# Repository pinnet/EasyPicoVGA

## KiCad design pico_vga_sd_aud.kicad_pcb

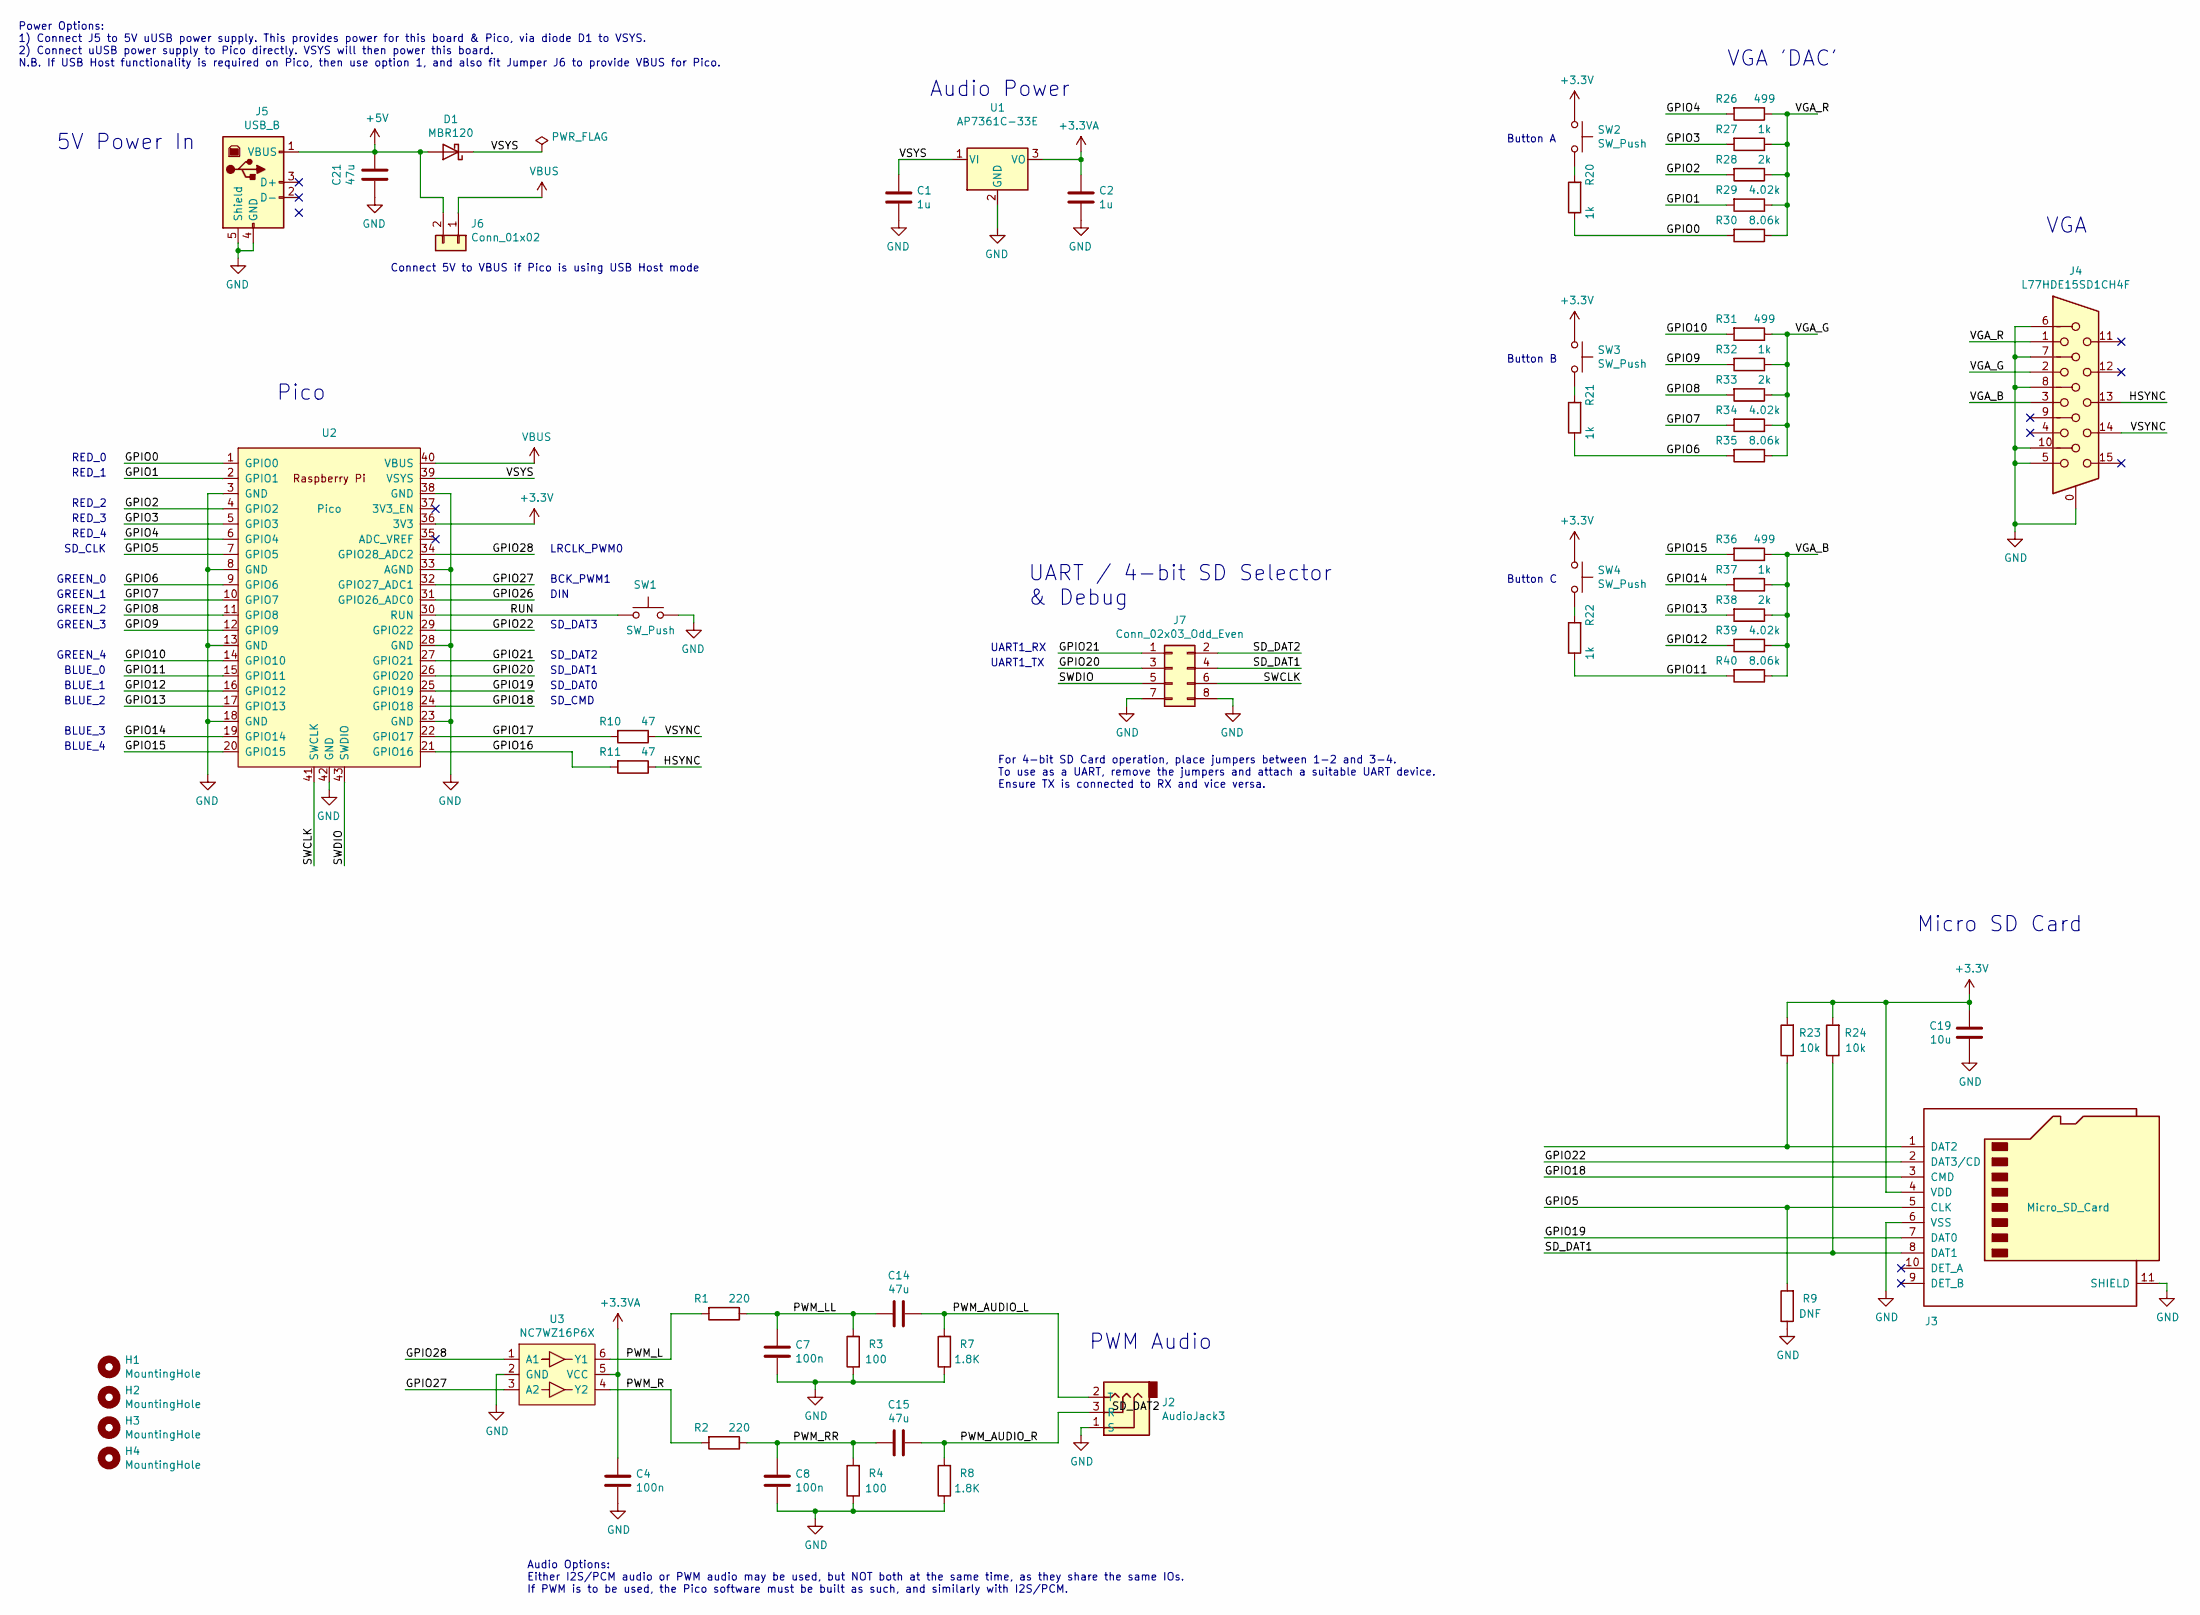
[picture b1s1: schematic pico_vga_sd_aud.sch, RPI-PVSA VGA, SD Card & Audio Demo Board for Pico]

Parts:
C1, C2: 1u; C_Disc_D4.7mm_W2.5mm_P5.00mm
C4, C7, C8: 100n; C_Disc_D4.7mm_W2.5mm_P5.00mm
C14, C15, C21: 47u; CP_Radial_D5.0mm_P2.50mm
C19: 10u; CP_Radial_D6.3mm_P2.50mm
D1: MBR120; D_A-405_P12.70mm_Horizontal
H1, H2, H3, H4: MountingHole; MountingHole_2.7mm_M2.5
J2: AudioJack3; CUI_SJ-3523-audio-jack
J3: Micro_SD_Card; microSD_HC_Molex_104031-0811
J4: L77HDE15SD1CH4F; DSUB-15-L77HDE15SD1CH4F
J5: USB_B; USB_B_Lumberg_2411_02_Horizontal
J6: Conn_01x02; PinHeader_1x02_P2.54mm_Vertical
J7: Conn_02x03_Odd_Even; PinHeader_2x04_P2.54mm_Vertical
R1, R2: 220; R_Axial_DIN0207_L6.3mm_D2.5mm_P15.24mm_Horizontal
R3, R4: 100; R_Axial_DIN0207_L6.3mm_D2.5mm_P15.24mm_Horizontal
R7, R8: 1.8K; R_Axial_DIN0207_L6.3mm_D2.5mm_P15.24mm_Horizontal
R9: DNF; R_Axial_DIN0207_L6.3mm_D2.5mm_P15.24mm_Horizontal
R10, R11: 47; R_Axial_DIN0207_L6.3mm_D2.5mm_P15.24mm_Horizontal
R20, R21, R22, R27, R32, R37: 1k; R_Axial_DIN0207_L6.3mm_D2.5mm_P15.24mm_Horizontal
R23, R24: 10k; R_Axial_DIN0207_L6.3mm_D2.5mm_P15.24mm_Horizontal
R26, R31, R36: 499; R_Axial_DIN0207_L6.3mm_D2.5mm_P15.24mm_Horizontal
R28, R33, R38: 2k; R_Axial_DIN0207_L6.3mm_D2.5mm_P15.24mm_Horizontal
R29, R34, R39: 4.02k; R_Axial_DIN0207_L6.3mm_D2.5mm_P15.24mm_Horizontal
R30, R35, R40: 8.06k; R_Axial_DIN0207_L6.3mm_D2.5mm_P15.24mm_Horizontal
SW1, SW2, SW3, SW4: SW_Push; SW_Tactile_SPST_Angled_PTS645Vx83-2LFS
U1: AP7361C-33E; TO-92_Inline
U2: Pico; RPi_Pico_SMD_TH
U3: NC7WZ16P6X; SOT-363_SC-70-6

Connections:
+3.3VA: C2.1, C4.1, U1.3 (VO), U3.5 (VCC)
+3V3: C19.1, J3.4 (VDD), R23.2, R24.2, SW2.1, SW3.1, SW4.1, U2.36 (3V3)
+5V: C21.1, D1.2 (A), J5.1 (VBUS), J6.2
/GPIO0: R20.1, R30.2, U2.1 (GPIO0)
/GPIO1: R29.2, U2.2 (GPIO1)
/GPIO2: R28.2, U2.4 (GPIO2)
/GPIO3: R27.2, U2.5 (GPIO3)
/GPIO4: R26.2, U2.6 (GPIO4)
/GPIO5: J3.5 (CLK), R9.2, U2.7 (GPIO5)
/GPIO6: R21.1, R35.2, U2.9 (GPIO6)
/GPIO7: R34.2, U2.10 (GPIO7)
/GPIO8: R33.2, U2.11 (GPIO8)
/GPIO9: R32.2, U2.12 (GPIO9)
/GPIO10: R31.2, U2.14 (GPIO10)
/GPIO11: R22.1, R40.2, U2.15 (GPIO11)
/GPIO12: R39.2, U2.16 (GPIO12)
/GPIO13: R38.2, U2.17 (GPIO13)
/GPIO14: R37.2, U2.19 (GPIO14)
/GPIO15: R36.2, U2.20 (GPIO15)
/GPIO16: R11.2, U2.21 (GPIO16)
/GPIO17: R10.2, U2.22 (GPIO17)
/GPIO18: J3.3 (CMD), U2.24 (GPIO18)
/GPIO19: J3.7 (DAT0), U2.25 (GPIO19)
/GPIO20: J7.3, U2.26 (GPIO20)
/GPIO21: J7.1, U2.27 (GPIO21)
/GPIO22: J3.2 (DAT3/CD), U2.29 (GPIO22)
/GPIO26: U2.31 (GPIO26_ADC0)
/GPIO27: U2.32 (GPIO27_ADC1), U3.3 (A2)
/GPIO28: U2.34 (GPIO28_ADC2), U3.1 (A1)
/HSYNC: J4.13, R11.1
/PWM_AUDIO_L: C14.1, J2.2 (T), R7.2
/PWM_AUDIO_R: C15.1, J2.3 (R), R8.2
/PWM_L: R1.2, U3.6 (Y1)
/PWM_LL: C7.1, C14.2, R1.1, R3.2
/PWM_R: R2.2, U3.4 (Y2)
/PWM_RR: C8.1, C15.2, R2.1, R4.2
/RUN: SW1.1, U2.30 (RUN)
/SD_DAT1: J3.8 (DAT1), J7.4, R24.1
/SD_DAT2: J7.2
/SWCLK: J7.6, U2.41 (SWCLK)
/SWDIO: J7.5, U2.43 (SWDIO)
/VGA_B: J4.3, R36.1, R37.1, R38.1, R39.1, R40.1
/VGA_G: J4.2, R31.1, R32.1, R33.1, R34.1, R35.1
/VGA_R: J4.1, R26.1, R27.1, R28.1, R29.1, R30.1
/VSYNC: J4.14, R10.1
/VSYS: C1.1, D1.1 (K), U1.1 (VI), U2.39 (VSYS)
GND: C1.2, C2.2, C4.2, C7.2, C8.2, C19.2, C21.2, J2.1 (S), J3.6 (VSS), J3.11 (SHIELD), J4.0, J4.5, J4.6, J4.7, J4.8, J4.10, J5.4 (GND), J5.5 (Shield), J7.7, J7.8, R3.1, R4.1, R7.1, R8.1, R9.1, SW1.2, U1.2 (GND), U2.3 (GND), U2.8 (GND), U2.13 (GND), U2.18 (GND), U2.23 (GND), U2.28 (GND), U2.33 (AGND), U2.38 (GND), U2.42 (GND), U3.2 (GND)
unnamed: J3.1 (DAT2), R23.1
unnamed: R20.2, SW2.2
unnamed: R21.2, SW3.2
unnamed: R22.2, SW4.2
VBUS: J6.1, U2.40 (VBUS)

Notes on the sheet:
Pico
Audio Power
PWM Audio
Micro SD Card
VGA
Connect 5V to VBUS if Pico is using USB Host mode
5V Power In
Power Options: 1) Connect J5 to 5V uUSB power supply. This provides power for this board & Pico, via diode D1 to VSYS. 2) Connect uUSB power supply to Pico directly. VSYS will then power this board. N.B. If USB Host functionality is required on Pico, then use option 1, and also fit Jumper J6 to pro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
VGA 'DAC'
Button A
Button B
Button C
SD_CLK
SD_CMD
SD_DAT0
SD_DAT1
SD_DAT2
SD_DAT3
DIN
BCK_PWM1
LRCLK_PWM0
RED_0
RED_1
RED_2
RED_3
RED_4
GREEN_0
GREEN_1
GREEN_2
GREEN_3
GREEN_4
BLUE_0
BLUE_1
BLUE_2
BLUE_3
BLUE_4
UART1_TX
UART1_RX
UART / 4-bit SD Selector & Debug
Audio Options: Either I2S/PCM audio or PWM audio may be used, but NOT both at the same time, as they share the same IOs. If PWM is to be used, the Pico software must be built as such, and similarly with I2S/PCM.

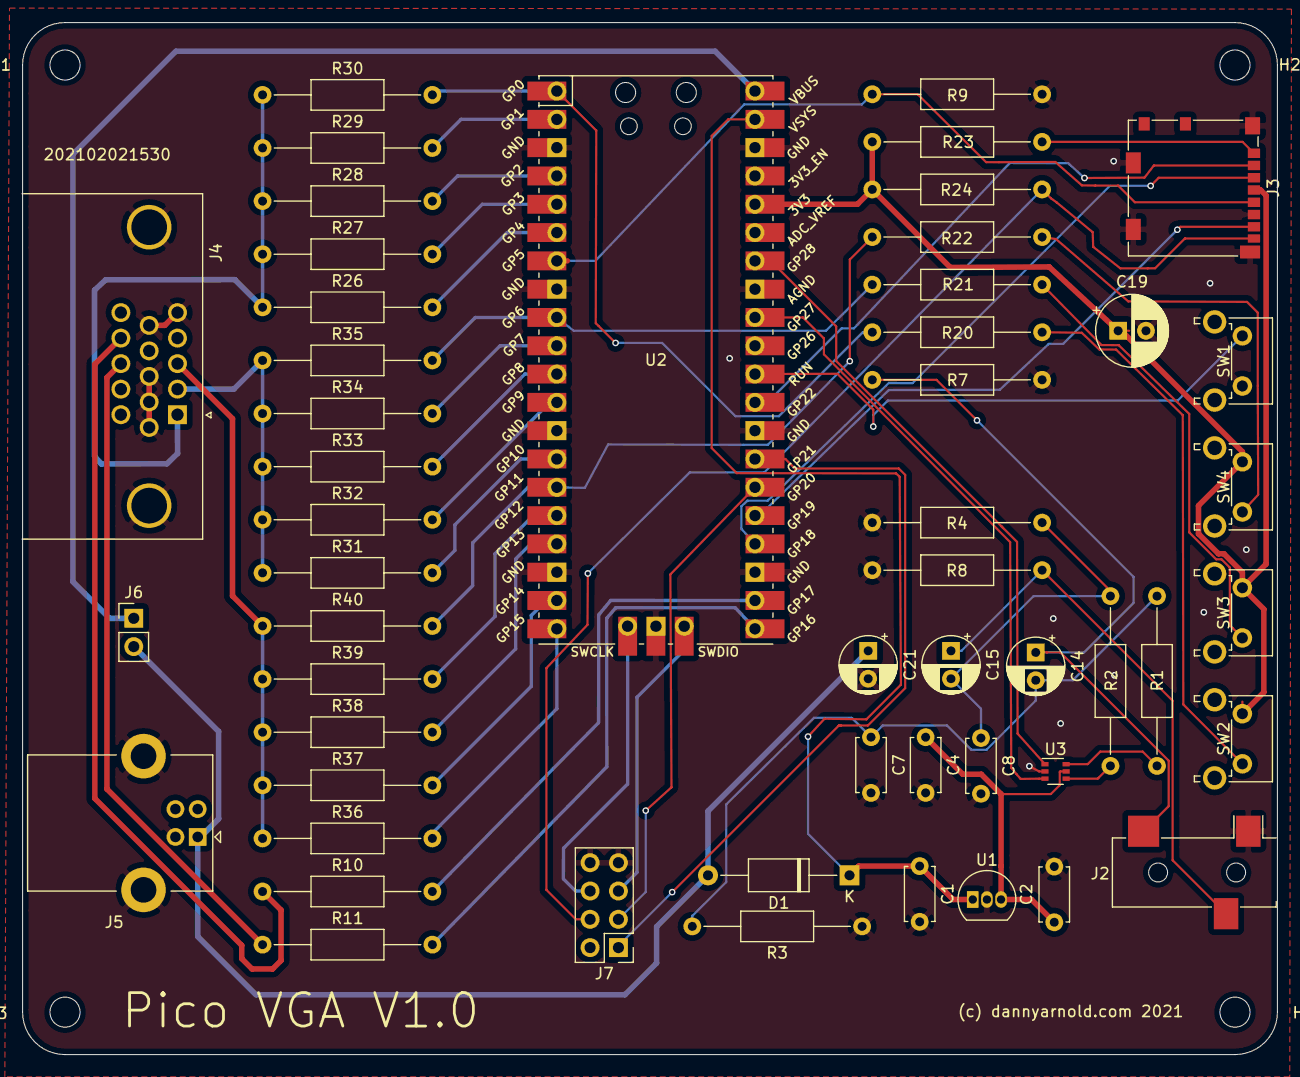
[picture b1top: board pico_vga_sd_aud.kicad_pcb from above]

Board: 2 copper layers, 112.6 x 92.6 mm, 56 parts (0 on the bottom side), 50 nets.
